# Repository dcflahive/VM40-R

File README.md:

# vm40
Hitachi Seiki VM40 Retrofit

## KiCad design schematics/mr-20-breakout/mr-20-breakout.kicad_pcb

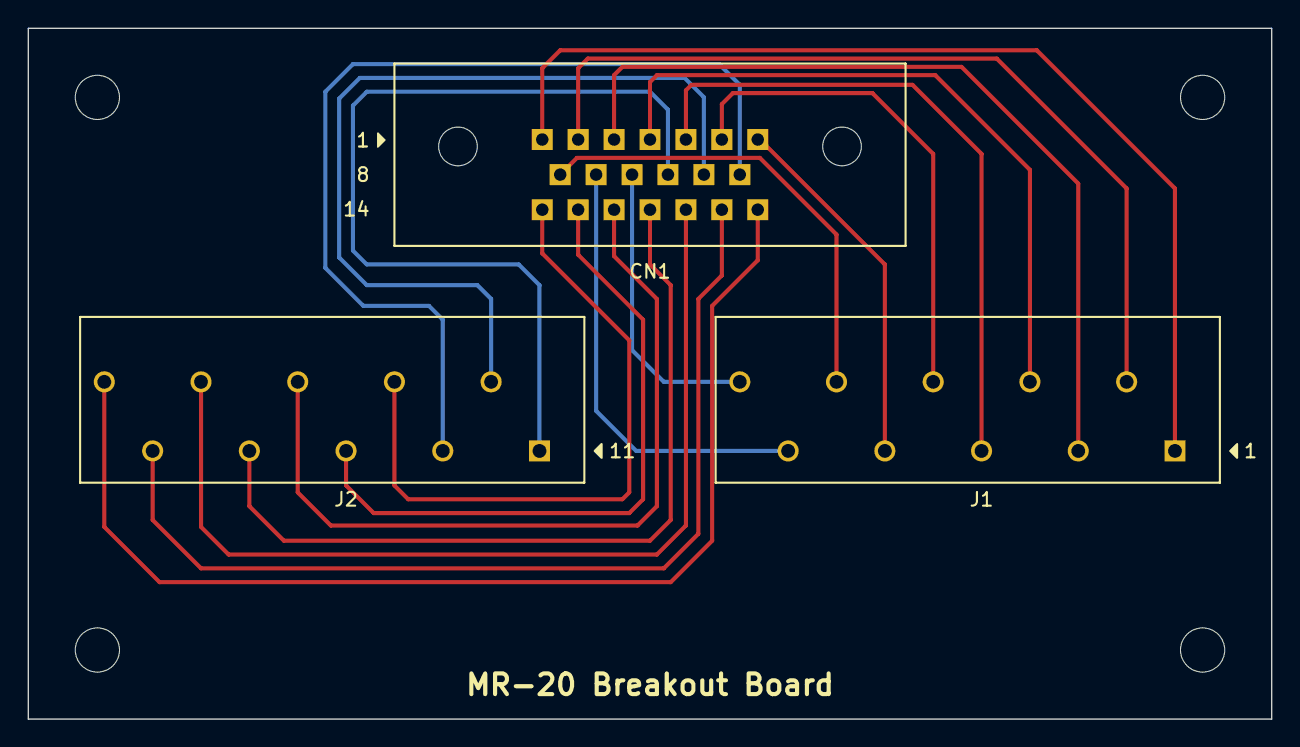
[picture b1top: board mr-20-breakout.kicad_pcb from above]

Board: 2 copper layers, 90.0 x 50.0 mm, 3 parts (0 on the bottom side), 20 nets.

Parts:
CN1: MR-20RMA+
J1, J2: PTSA-1.5-10-3.5-Z; PhoenixContact_PTSA_1,5_10_3,5-Z

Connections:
unnamed: CN1.1, J1.1
unnamed: CN1.2, J1.2
unnamed: CN1.3, J1.3
unnamed: CN1.4, J1.4
unnamed: CN1.5, J1.5
unnamed: CN1.6, J1.6
unnamed: CN1.7, J1.7
unnamed: CN1.8, J1.8
unnamed: CN1.9, J1.9
unnamed: CN1.10, J1.10
unnamed: CN1.11, J2.1
unnamed: CN1.12, J2.2
unnamed: CN1.13, J2.3
unnamed: CN1.14, J2.4
unnamed: CN1.15, J2.5
unnamed: CN1.16, J2.6
unnamed: CN1.17, J2.7
unnamed: CN1.18, J2.8
unnamed: CN1.19, J2.9
unnamed: CN1.20, J2.10

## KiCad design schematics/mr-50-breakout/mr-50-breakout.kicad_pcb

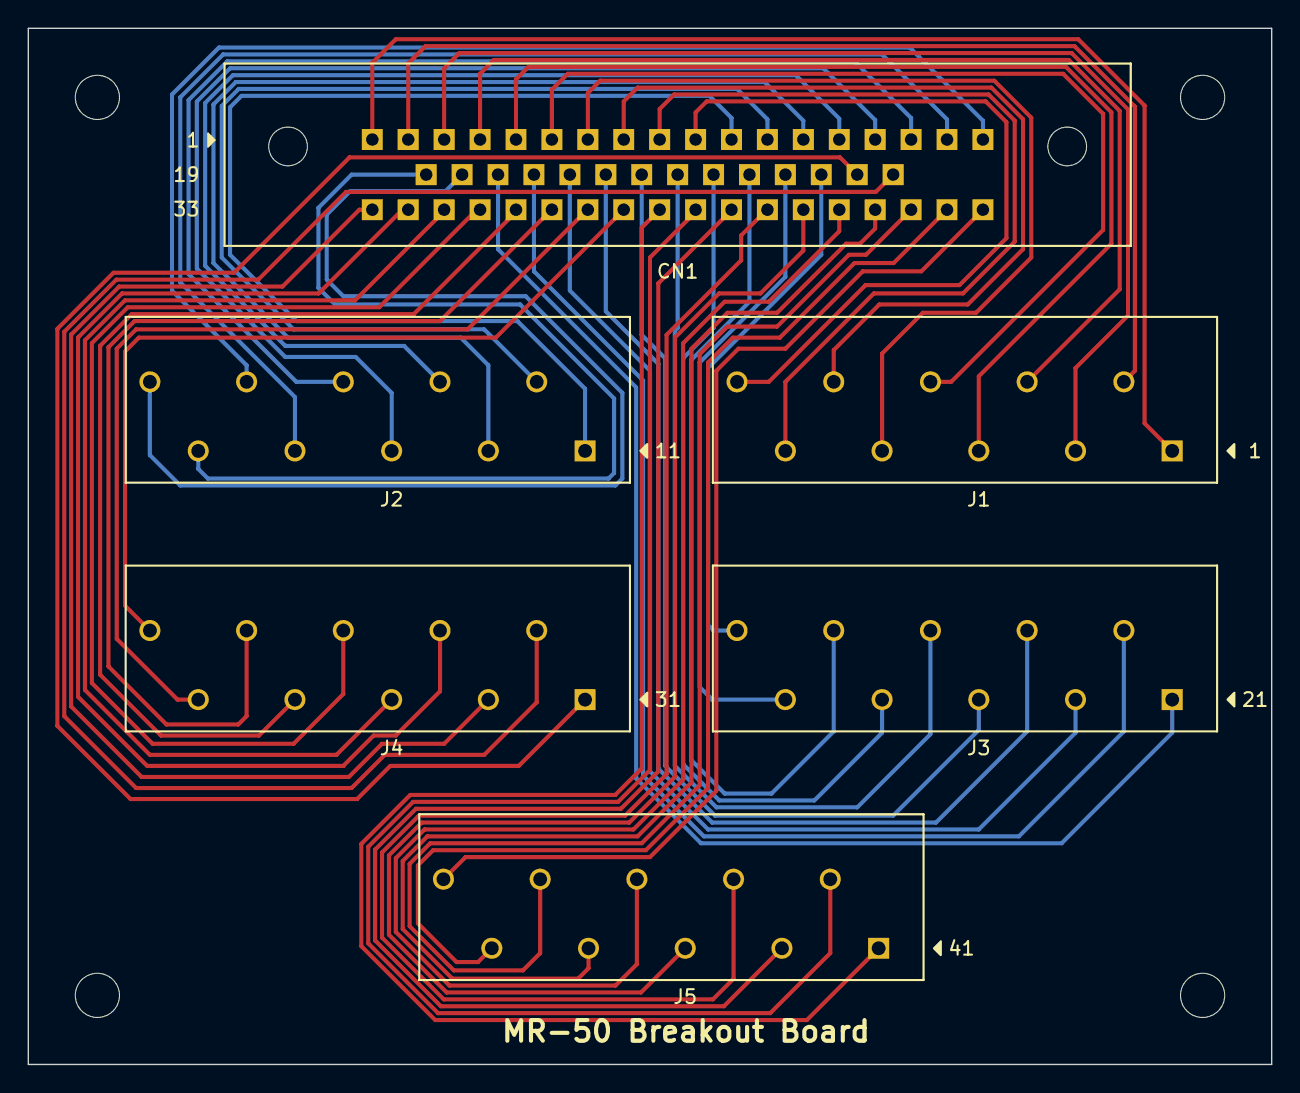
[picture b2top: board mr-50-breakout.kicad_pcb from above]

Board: 2 copper layers, 90.0 x 75.0 mm, 6 parts (0 on the bottom side), 50 nets.

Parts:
CN1: MR-50RMA+
J1, J2, J3, J4, J5: PTSA-1.5-10-3.5-Z; PhoenixContact_PTSA_1,5_10_3,5-Z

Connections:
unnamed: CN1.1, J1.1
unnamed: CN1.2, J1.2
unnamed: CN1.3, J1.3
unnamed: CN1.4, J1.4
unnamed: CN1.5, J1.5
unnamed: CN1.6, J1.6
unnamed: CN1.7, J1.7
unnamed: CN1.8, J1.8
unnamed: CN1.9, J1.9
unnamed: CN1.10, J1.10
unnamed: CN1.11, J2.1
unnamed: CN1.12, J2.2
unnamed: CN1.13, J2.3
unnamed: CN1.14, J2.4
unnamed: CN1.15, J2.5
unnamed: CN1.16, J2.6
unnamed: CN1.17, J2.7
unnamed: CN1.18, J2.8
unnamed: CN1.19, J2.9
unnamed: CN1.20, J2.10
unnamed: CN1.21, J3.1
unnamed: CN1.22, J3.2
unnamed: CN1.23, J3.3
unnamed: CN1.24, J3.4
unnamed: CN1.25, J3.5
unnamed: CN1.26, J3.6
unnamed: CN1.27, J3.7
unnamed: CN1.28, J3.8
unnamed: CN1.29, J3.9
unnamed: CN1.30, J3.10
unnamed: CN1.31, J4.1
unnamed: CN1.32, J4.2
unnamed: CN1.33, J4.3
unnamed: CN1.34, J4.4
unnamed: CN1.35, J4.5
unnamed: CN1.36, J4.6
unnamed: CN1.37, J4.7
unnamed: CN1.38, J4.8
unnamed: CN1.39, J4.9
unnamed: CN1.40, J4.10
unnamed: CN1.41, J5.1
unnamed: CN1.42, J5.2
unnamed: CN1.43, J5.3
unnamed: CN1.44, J5.4
unnamed: CN1.45, J5.5
unnamed: CN1.46, J5.6
unnamed: CN1.47, J5.7
unnamed: CN1.48, J5.8
unnamed: CN1.49, J5.9
unnamed: CN1.50, J5.10

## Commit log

2020-06-12 Add docs
2022-03-14 Initial wiring diagram
2022-05-07 Added breakout board schematics, LinuxCNC baseline config, BOM
2022-05-07 Added MR-20 breakout board schematics
